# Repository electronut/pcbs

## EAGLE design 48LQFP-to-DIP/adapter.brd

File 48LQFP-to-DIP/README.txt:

Design files for a 48LQFP to DIP adapter. I needed such an adapter for prototyping with some ARM Cortex M4 chips, and since I couldn't find a suitable adapter here in India, I decided to try and make one.

This work is licensed under the Creative Commons Attribution 4.0 International License. To view a copy of this license, visit http://creativecommons.org/licenses/by/4.0/.

Mahesh Venkitachalam
electronut.in

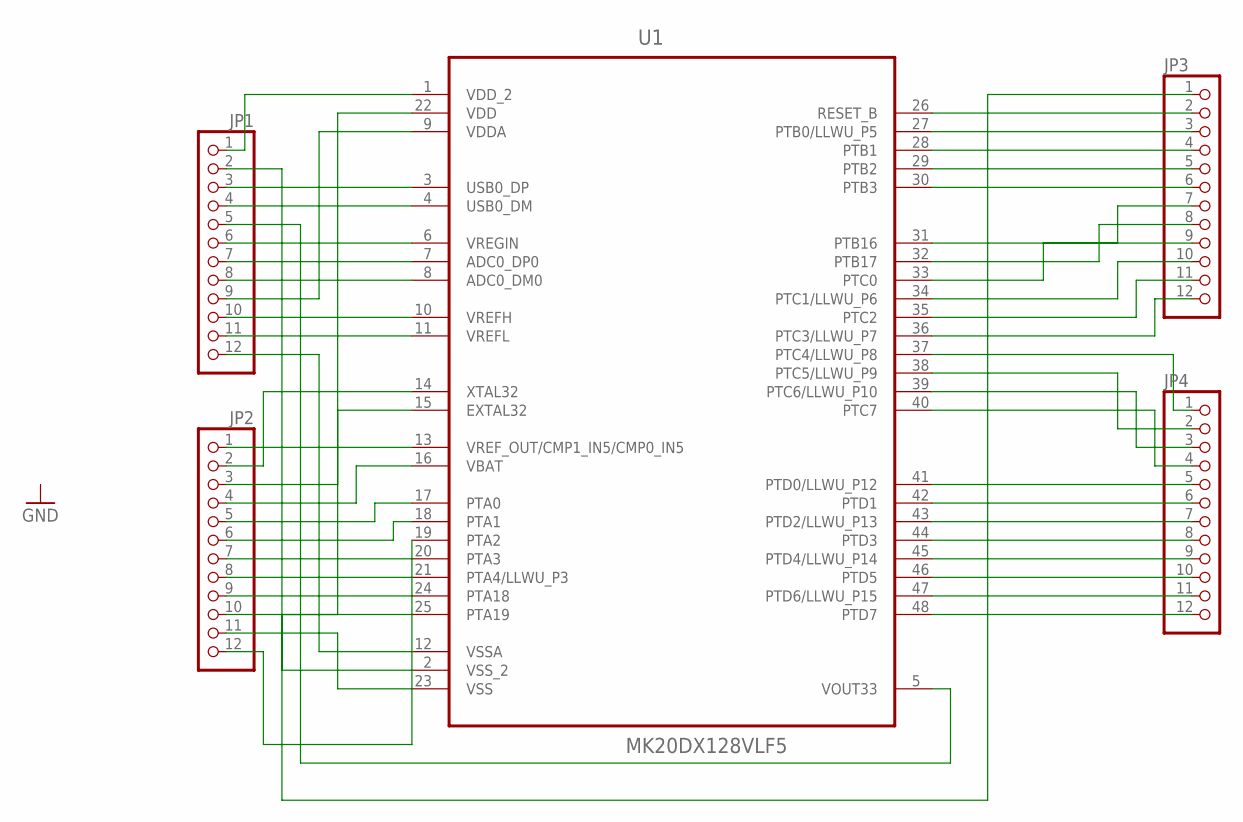
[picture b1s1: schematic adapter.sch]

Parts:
JP1, JP2, JP3, JP4: PINHD-1X12-CB; 1X12-CB
U1: MK20DX128VLF5; QFP50P900X900X160-48N

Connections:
unnamed: JP1.1, U1.1 (VDD_2)
unnamed: JP1.2, U1.2 (VSS_2)
unnamed: JP1.3, U1.3 (USB0_DP)
unnamed: JP1.4, U1.4 (USB0_DM)
unnamed: JP1.5, U1.5 (VOUT33)
unnamed: JP1.6, U1.6 (VREGIN)
unnamed: JP1.7, U1.7 (ADC0_DP0)
unnamed: JP1.8, U1.8 (ADC0_DM0)
unnamed: JP1.9, U1.9 (VDDA)
unnamed: JP1.10, U1.10 (VREFH)
unnamed: JP1.11, U1.11 (VREFL)
unnamed: JP1.12, U1.12 (VSSA)
unnamed: JP2.1, U1.13 (VREF_OUT/CMP1_IN5/CMP0_IN5)
unnamed: JP2.2, U1.14 (XTAL32)
unnamed: JP2.3, U1.15 (EXTAL32)
unnamed: JP2.4, U1.16 (VBAT)
unnamed: JP2.5, U1.17 (PTA0)
unnamed: JP2.6, U1.18 (PTA1)
unnamed: JP2.7, U1.19 (PTA2)
unnamed: JP2.8, U1.20 (PTA3)
unnamed: JP2.9, U1.21 (PTA4/LLWU_P3)
unnamed: JP2.10, U1.22 (VDD)
unnamed: JP2.11, U1.23 (VSS)
unnamed: JP2.12, U1.24 (PTA18)
unnamed: JP3.1, U1.25 (PTA19)
unnamed: JP3.2, U1.26 (RESET_B)
unnamed: JP3.3, U1.27 (PTB0/LLWU_P5)
unnamed: JP3.4, U1.28 (PTB1)
unnamed: JP3.5, U1.29 (PTB2)
unnamed: JP3.6, U1.30 (PTB3)
unnamed: JP3.7, U1.31 (PTB16)
unnamed: JP3.8, U1.32 (PTB17)
unnamed: JP3.9, U1.33 (PTC0)
unnamed: JP3.10, U1.34 (PTC1/LLWU_P6)
unnamed: JP3.11, U1.35 (PTC2)
unnamed: JP3.12, U1.36 (PTC3/LLWU_P7)
unnamed: JP4.5, U1.41 (PTD0/LLWU_P12)
unnamed: JP4.6, U1.42 (PTD1)
unnamed: JP4.7, U1.43 (PTD2/LLWU_P13)
unnamed: JP4.8, U1.44 (PTD3)
unnamed: JP4.9, U1.45 (PTD4/LLWU_P14)
unnamed: JP4.10, U1.46 (PTD5)
unnamed: JP4.11, U1.47 (PTD6/LLWU_P15)
unnamed: JP4.12, U1.48 (PTD7)
unnamed: JP4.4, U1.40 (PTC7)
unnamed: JP4.3, U1.39 (PTC6/LLWU_P10)
unnamed: JP4.2, U1.38 (PTC5/LLWU_P9)
unnamed: JP4.1, U1.37 (PTC4/LLWU_P8)

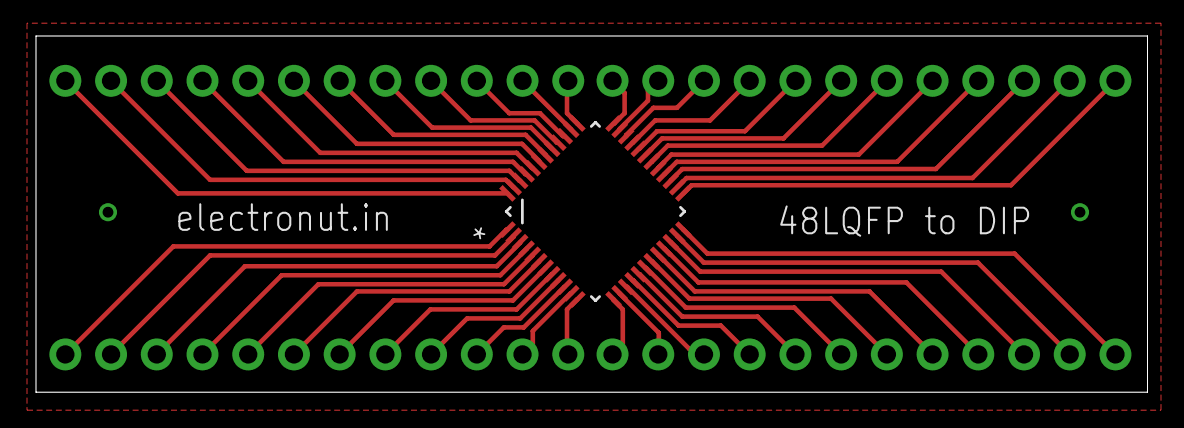
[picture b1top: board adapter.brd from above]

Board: 2 copper layers, 61.8 x 19.8 mm, 5 parts (0 on the bottom side), 48 nets.

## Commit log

2014-05-04 pcbs desgns
2014-05-04 added readme
